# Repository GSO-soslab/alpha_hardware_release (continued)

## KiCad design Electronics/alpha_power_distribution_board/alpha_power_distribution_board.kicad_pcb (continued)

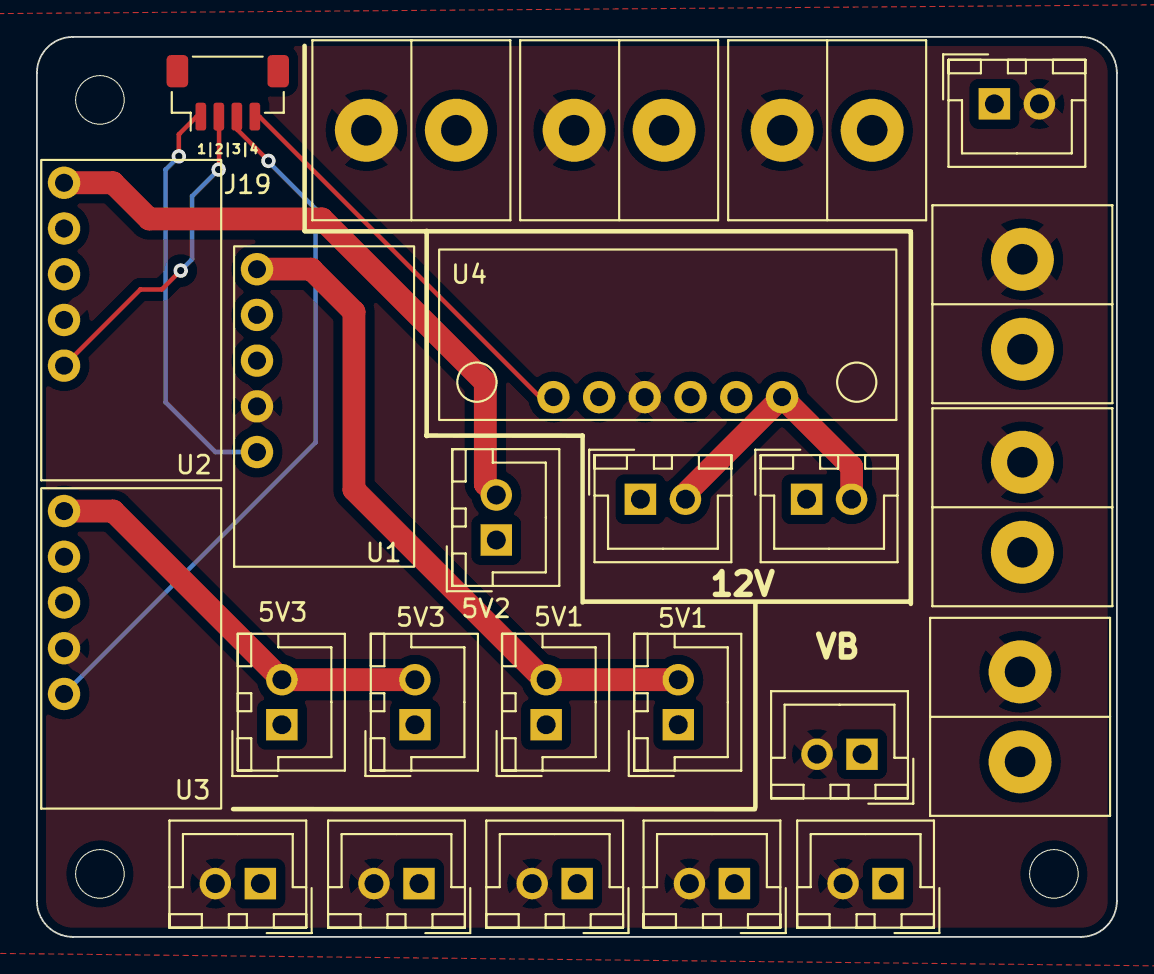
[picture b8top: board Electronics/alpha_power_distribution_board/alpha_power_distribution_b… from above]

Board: 2 copper layers, 60.0 x 50.0 mm, 28 parts (0 on the bottom side), 10 nets.

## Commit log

2023-09-07 electronics release 1.0
2023-09-07 added readme for electronics
2023-09-07 update readme links
2023-09-07 added pdf
2023-09-07 added pdf links
2023-09-07 added readme
2023-09-07 small change
2023-09-07 electronics doc update
2023-09-07 remove GPL license
2023-09-07 Create LICENSE
2023-09-07 added award grant and license
2023-09-07 alpha auv stand step file uploaded
2023-09-07 added stand diagram photo
2023-09-07 UPDATED README OF THE SBC HAT
2023-09-09 uploaded frame and vertical thruster
2023-09-10 Updated fairing cad folder
2023-09-10 put schematics into a folder
2023-09-10 update schematics links
2023-09-10 small update on readme
2023-09-10 updated surge thruster and lifting plate
2023-09-10 Added ping360 and dvl plate information
2023-09-10 add subfolders
2023-09-10 Added part list and updated part number
2023-10-15 Updated pcb
2023-10-15 Added electronics diagrams for endcap and internal housing
2023-11-16 updated power distribuiotn and esc board
2024-03-24 updated PI setup guide
2024-06-03 added three new boards, and readme files
2024-06-03 added v2 endcap diagram
2024-06-03 updated diagram
2024-09-20 update electronics files to the newest version
2024-09-20 remove icon file
2024-09-20 added SBC_MK2 document
2024-10-07 Update PI_setup_guide.md
    update time sync instructions
